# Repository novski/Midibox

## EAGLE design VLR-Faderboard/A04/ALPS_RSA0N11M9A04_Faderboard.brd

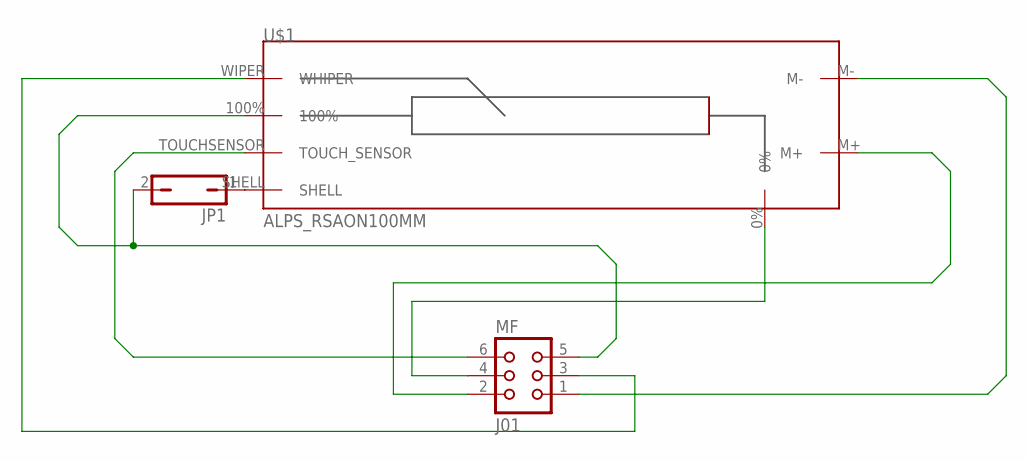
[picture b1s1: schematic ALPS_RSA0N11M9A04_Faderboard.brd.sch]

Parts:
JP1: JP1Q; JP1
MF: J01; CON06
U$1: ALPS_RSAON100MM; ALPS_RAS0N_MOTOR-FADER

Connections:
unnamed: MF.1, U$1.M-
unnamed: MF.2, U$1.M+
unnamed: MF.3, U$1.WIPER (WHIPER)
unnamed: MF.4, U$1.0%
unnamed: JP1.2, MF.5, U$1.100%
unnamed: MF.6, U$1.TOUCHSENSOR (TOUCH_SENSOR)
unnamed: JP1.1, U$1.SHELL

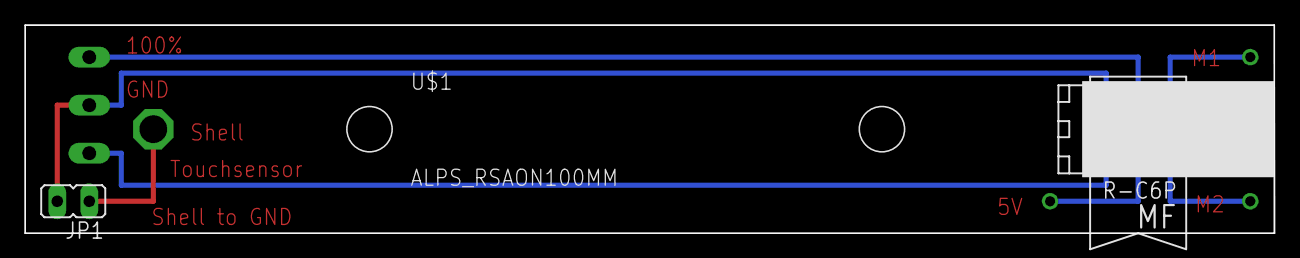
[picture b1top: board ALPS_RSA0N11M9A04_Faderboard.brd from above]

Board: 2 copper layers, 99.1 x 16.5 mm, 3 parts (0 on the bottom side), 7 nets.

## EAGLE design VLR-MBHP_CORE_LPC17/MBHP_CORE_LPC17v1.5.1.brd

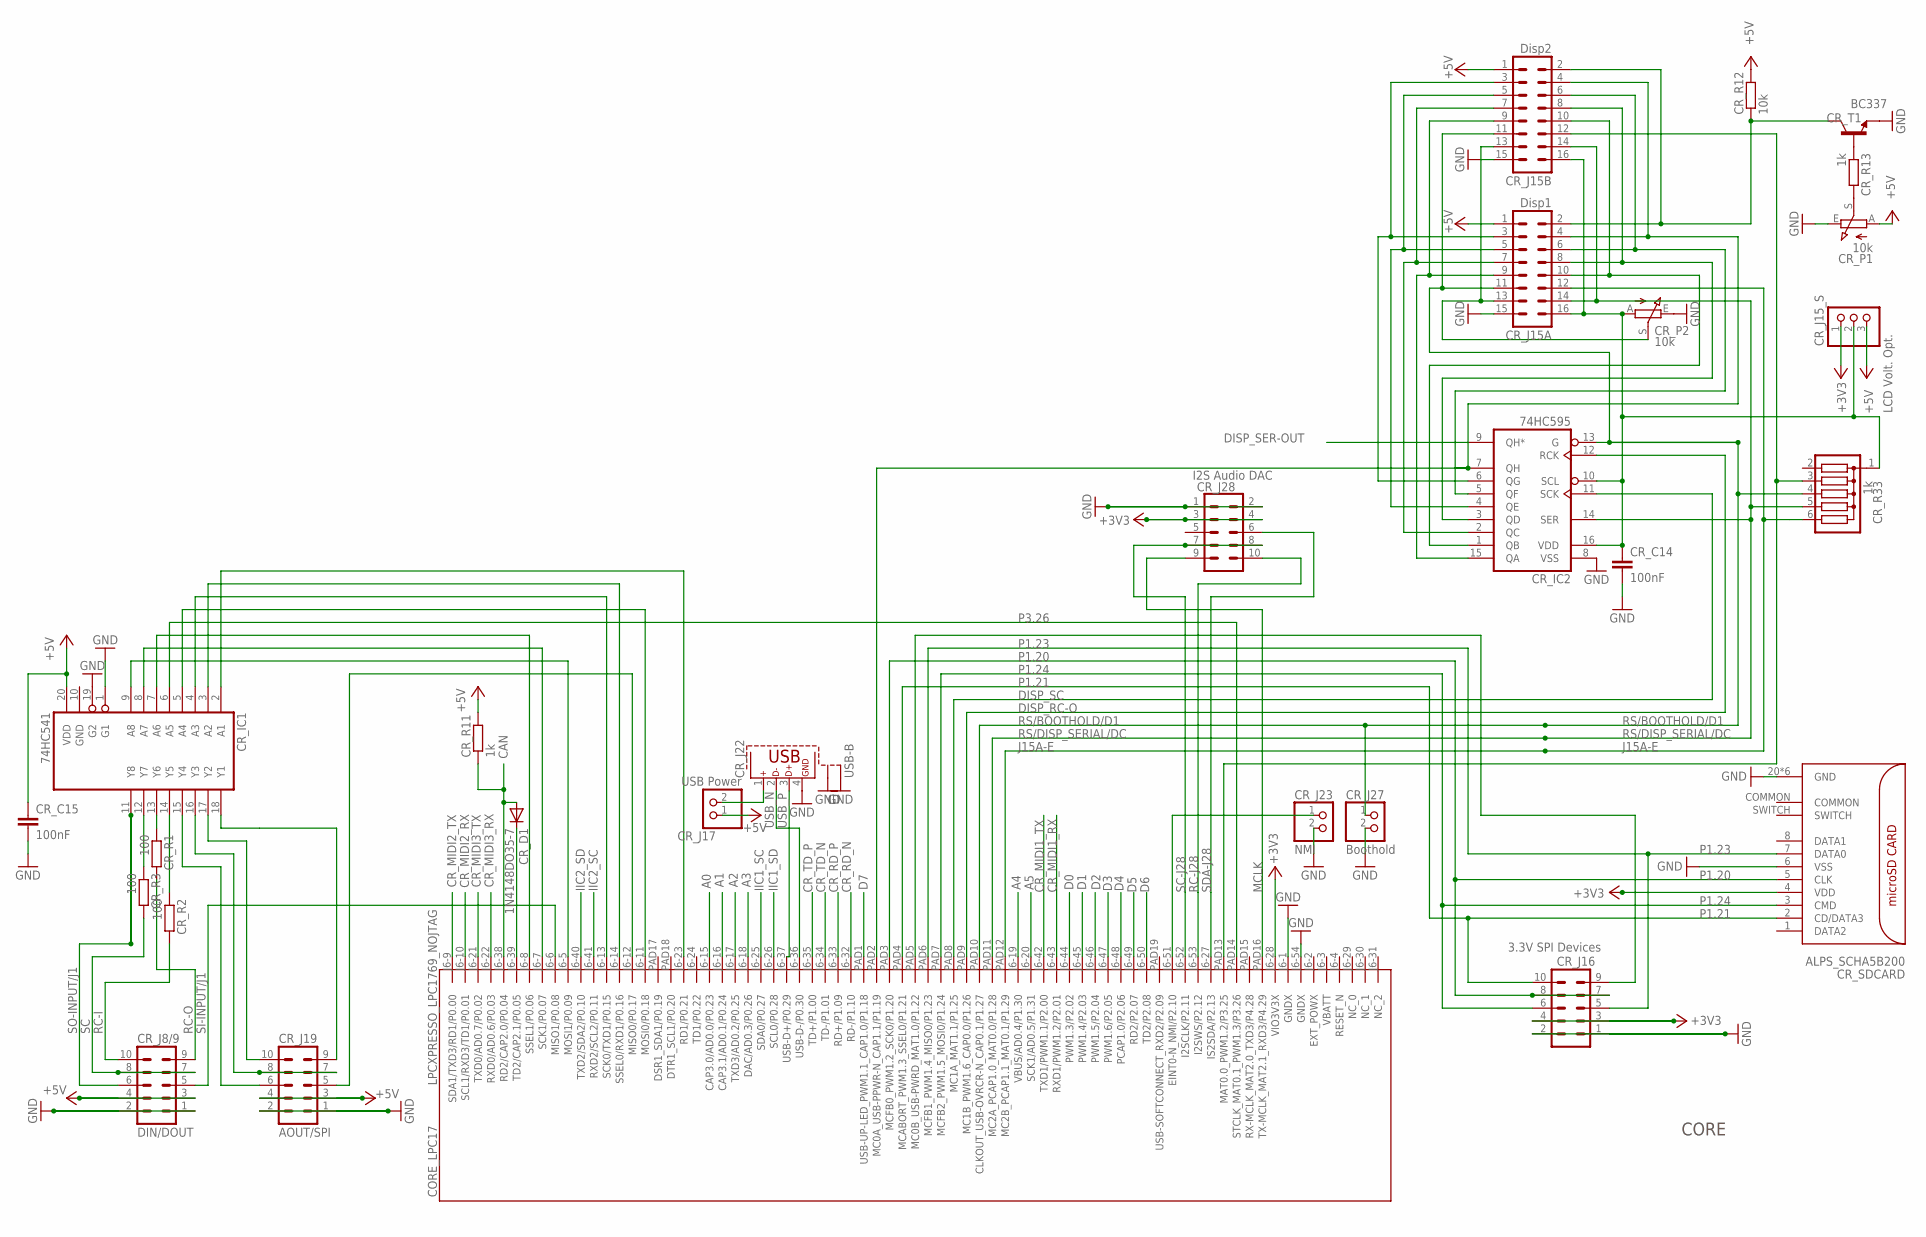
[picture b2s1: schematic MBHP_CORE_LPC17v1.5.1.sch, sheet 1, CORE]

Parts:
CORE_LPC17: LPCXPRESSO_LPC1769_NOJTAG; LPCEXPRESSO_CUT_NOJTAG
CR_C14, CR_C15: 100nF; C5B3
CR_D1: 1N4148DO35-7; DO35-7
CR_IC1: 74HC541; DIL20
CR_IC2: 74HC595; DIL16
CR_J8/9: DIN/DOUT; ML10
CR_J15A: Disp1; ML16
CR_J15B: Disp2; ML16
CR_J15_S: LCD Volt. Opt.; 1X03
CR_J16: 3.3V SPI Devices; ML10
CR_J17: USB Power; 1X02
CR_J19: AOUT/SPI; ML10
CR_J22: USB-B
CR_J23: NMI; 1X02
CR_J27: Boothold; 1X02
CR_J28: I2S Audio DAC; ML10
CR_P1, CR_P2: 10k; 6MM_V
CR_R1, CR_R2, CR_R3: 100; 0204/7
CR_R11, CR_R13: 1k; 0204/7
CR_R12: 10k; 0204/7
CR_R33: 1k; SIL6
CR_SDCARD: ALPS_SCHA5B200; ALPS_SCHA5B0200_MICRO_SD_PUSHPUSH
CR_T1: BC337; TO92

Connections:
+3V3: CORE_LPC17.J6-28 (VIO3V3X), CR_J15_S.1, CR_J16.3, CR_J16.4, CR_J28.3, CR_J28.4, CR_SDCARD.4 (VDD); also elsewhere on the board
+5V: CR_C15.1, CR_IC1.20 (VDD), CR_J8/9.3, CR_J8/9.4, CR_J15A.1, CR_J15B.1, CR_J15_S.3, CR_J17.1, CR_J19.3, CR_J19.4, CR_P1.A, CR_R11.2, CR_R12.2; also elsewhere on the board
A0: CORE_LPC17.J6-15 (CAP3.0/AD0.0/P0.23); also elsewhere on the board
A1: CORE_LPC17.J6-16 (CAP3.1/AD0.1/P0.24); also elsewhere on the board
A2: CORE_LPC17.J6-17 (TXD3/AD0.2/P0.25); also elsewhere on the board
A3: CORE_LPC17.J6-18 (DAC/AD0.3/P0.26); also elsewhere on the board
A4: CORE_LPC17.J6-19 (VBUS/AD0.4/P1.30); also elsewhere on the board
A5: CORE_LPC17.J6-20 (SCK1/AD0.5/P1.31); also elsewhere on the board
CAN: CORE_LPC17.J6-38 (RD2/CAP2.0/P0.04), CR_D1.A, CR_R11.1; also elsewhere on the board
CR_MIDI1_RX: CORE_LPC17.J6-43 (RXD1/PWM1.2/P2.01); also elsewhere on the board
CR_MIDI1_TX: CORE_LPC17.J6-42 (TXD1/PWM1.1/P2.00); also elsewhere on the board
CR_MIDI2_RX: CORE_LPC17.J6-10 (SCL1/RXD3/TD1/P0.01); also elsewhere on the board
CR_MIDI2_TX: CORE_LPC17.J6-9 (SDA1/TXD3/RD1/P0.00); also elsewhere on the board
CR_MIDI3_RX: CORE_LPC17.J6-22 (RXD0/AD0.6/P0.03); also elsewhere on the board
CR_MIDI3_TX: CORE_LPC17.J6-21 (TXD0/AD0.7/P0.02); also elsewhere on the board
CR_RD_N: CORE_LPC17.J6-32 (RD-/P1.10); also elsewhere on the board
CR_RD_P: CORE_LPC17.J6-33 (RD+/P1.09); also elsewhere on the board
CR_TD_N: CORE_LPC17.J6-34 (TD-/P1.01); also elsewhere on the board
CR_TD_P: CORE_LPC17.J6-35 (TD+/P1.00); also elsewhere on the board
D0: CORE_LPC17.J6-44 (PWM1.3/P2.02); also elsewhere on the board
D1: CORE_LPC17.J6-45 (PWM1.4/P2.03); also elsewhere on the board
D2: CORE_LPC17.J6-46 (PWM1.5/P2.04); also elsewhere on the board
D3: CORE_LPC17.J6-47 (PWM1.6/P2.05); also elsewhere on the board
D4: CORE_LPC17.J6-48 (PCAP1.0/P2.06); also elsewhere on the board
D5: CORE_LPC17.J6-49 (RD2/P2.07); also elsewhere on the board
D6: CORE_LPC17.J6-50 (TD2/P2.08); also elsewhere on the board
D7: CORE_LPC17.PAD1 (USB-UP-LED_PWM1.1_CAP1.0/P1.18); also elsewhere on the board
DISP_RC-O: CORE_LPC17.PAD9 (MC1B_PWM1.6_CAP0.0/P1.26), CR_IC2.12 (RCK)
DISP_SC: CORE_LPC17.PAD8 (MC1A_MAT1.1/P1.25), CR_IC2.11 (SCK)
DISP_SER-OUT: CR_IC2.9 (QH*)
GND: CORE_LPC17.J6-1 (GNDX), CORE_LPC17.J6-54 (GNDX), CR_C14.2, CR_C15.2, CR_IC1.1 (G1), CR_IC1.10 (GND), CR_IC1.19 (G2), CR_IC2.8 (VSS), CR_J8/9.1, CR_J8/9.2, CR_J15A.15, CR_J15B.15, CR_J16.1, CR_J16.2, CR_J19.1, CR_J19.2, CR_J22.4, CR_J22.S1, CR_J22.S2, CR_J23.2, CR_J27.2, CR_J28.1, CR_J28.2, CR_P1.E, CR_P2.E, CR_SDCARD.6 (VSS), CR_SDCARD.20 (GND), CR_SDCARD.21 (GND), CR_SDCARD.22 (GND), CR_SDCARD.23 (GND), CR_SDCARD.24 (GND), CR_SDCARD.25 (GND), CR_T1.1 (E); also elsewhere on the board
IIC1_SC: CORE_LPC17.J6-25 (SDA0/P0.27); also elsewhere on the board
IIC1_SD: CORE_LPC17.J6-26 (SCL0/P0.28); also elsewhere on the board
IIC2_SC: CORE_LPC17.J6-41 (RXD2/SCL2/P0.11); also elsewhere on the board
IIC2_SD: CORE_LPC17.J6-40 (TXD2/SDA2/P0.10); also elsewhere on the board
J15A-E: CORE_LPC17.PAD12 (MC2B_PCAP1.1_MAT0.1/P1.29), CR_J15A.12, CR_R33.6
J15B-E2: CORE_LPC17.PAD13 (MAT0.0_PWM1.2/P3.25), CR_J15B.12, CR_R33.3; also elsewhere on the board
LCD_VOLTAGE_OPTION: CR_C14.1, CR_IC2.10 (SCL), CR_IC2.16 (VDD), CR_J15A.16, CR_J15B.16, CR_J15_S.2, CR_P2.A, CR_R33.1; also elsewhere on the board
MCLK: CORE_LPC17.PAD16 (TX-MCLK_MAT2.1_RXD3/P4.29), CR_J28.9
unnamed: CR_IC2.6 (QG), CR_J15A.3, CR_J15B.3
unnamed: CR_IC2.5 (QF), CR_J15A.6, CR_J15B.6
unnamed: CR_IC2.4 (QE), CR_J15A.5, CR_J15B.5
unnamed: CR_IC2.3 (QD), CR_J15A.8, CR_J15B.8
unnamed: CORE_LPC17.J6-39 (TD2/CAP2.1/P0.05), CR_D1.C
unnamed: CR_IC2.2 (QC), CR_J15A.7, CR_J15B.7
unnamed: CR_IC2.1 (QB), CR_J15A.10, CR_J15B.10
unnamed: CR_IC2.15 (QA), CR_J15A.9, CR_J15B.9
unnamed: CORE_LPC17.J6-51 (EINT0-N_NMI/P2.10), CR_J23.1
unnamed: CR_J15A.13, CR_J15B.13, CR_P2.S
unnamed: CR_IC1.15 (Y4), CR_J19.6
unnamed: CR_P1.S, CR_R13.2
unnamed: CR_R13.1, CR_T1.2 (B)
unnamed: CR_J15A.2, CR_J15B.2, CR_R12.1, CR_T1.3 (C)
unnamed: CR_IC1.17 (Y2), CR_J19.10
unnamed: CR_IC1.18 (Y1), CR_J19.9
unnamed: CR_IC1.16 (Y3), CR_J19.7, CR_J19.8
unnamed: CORE_LPC17.J6-12 (MISO0/P0.17), CR_J19.5
unnamed: CORE_LPC17.PAD5 (MC0B_USB-PWRD_MAT1.0/P1.22), CR_J16.9
unnamed: CR_J17.2, CR_J22.1
unnamed: CORE_LPC17.PAD2 (MC0A_USB-PPWR-N_CAP1.1/P1.19), CR_IC2.7 (QH), CR_J15A.4, CR_J15B.4
unnamed: CORE_LPC17.J6-14 (SSEL0/RXD1/P0.16), CR_IC1.3 (A2)
unnamed: CORE_LPC17.J6-23 (RD1/P0.21), CR_IC1.2 (A1)
unnamed: CORE_LPC17.J6-13 (SCK0/TXD1/P0.15), CR_IC1.4 (A3)
unnamed: CORE_LPC17.J6-11 (MOSI0/P0.18), CR_IC1.5 (A4)
unnamed: CORE_LPC17.J6-8 (SSEL1/P0.06), CR_IC1.7 (A6)
unnamed: CORE_LPC17.J6-7 (SCK1/P0.07), CR_IC1.8 (A7)
unnamed: CORE_LPC17.J6-5 (MOSI1/P0.09), CR_IC1.9 (A8)
P1.20: CORE_LPC17.PAD3 (MCFB0_PWM1.2_SCK0/P1.20), CR_J16.7, CR_J16.8, CR_SDCARD.5 (CLK)
P1.21: CORE_LPC17.PAD4 (MCABORT_PWM1.3_SSEL0/P1.21), CR_J16.10, CR_SDCARD.2 (CD/DATA3)
P1.23: CORE_LPC17.PAD6 (MCFB1_PWM1.4_MISO0/P1.23), CR_J16.5, CR_SDCARD.7 (DATA0)
P1.24: CORE_LPC17.PAD7 (MCFB2_PWM1.5_MOSI0/P1.24), CR_J16.6, CR_SDCARD.3 (CMD)
P3.26: CORE_LPC17.PAD14 (STCLK_MAT0.1_PWM1.3/P3.26), CR_IC1.6 (A5)
RC-I: CR_J8/9.10, CR_R2.2
RC-I-: CR_IC1.14 (Y5), CR_R2.1
RC-J28: CORE_LPC17.J6-53 (I2SWS/P2.12), CR_J28.10; also elsewhere on the board
RC-O: CR_J8/9.9, CR_R1.2
RC-O-: CR_IC1.13 (Y6), CR_R1.1
RS/BOOTHOLD/D1: CORE_LPC17.PAD10 (CLKOUT_USB-OVRCR-N_CAP0.1/P1.27), CR_IC2.13 (G), CR_J15A.11, CR_J15B.11, CR_J27.1, CR_R33.4; also elsewhere on the board
RS/DISP_SERIAL/DC: CORE_LPC17.PAD11 (MC2A_PCAP1.0_MAT0.0/P1.28), CR_IC2.14 (SER), CR_J15A.14, CR_J15B.14, CR_R33.5; also elsewhere on the board
SC: CR_J8/9.7, CR_J8/9.8, CR_R3.2
SC-: CR_IC1.12 (Y7), CR_R3.1
SC-J28: CORE_LPC17.J6-52 (I2SCLK/P2.11), CR_J28.7, CR_J28.8; also elsewhere on the board
SDA-J28: CORE_LPC17.J6-27 (IS2SDA/P2.13), CR_J28.6; also elsewhere on the board
SI-INPUT/J1: CORE_LPC17.J6-6 (MISO1/P0.08), CR_J8/9.5
SO-INPUT/J1: CR_IC1.11 (Y8), CR_J8/9.6
USB_N: CORE_LPC17.J6-36 (USB-D-/P0.30), CR_J22.2
USB_P: CORE_LPC17.J6-37 (USB-D+/P0.29), CR_J22.3

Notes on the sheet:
CORE

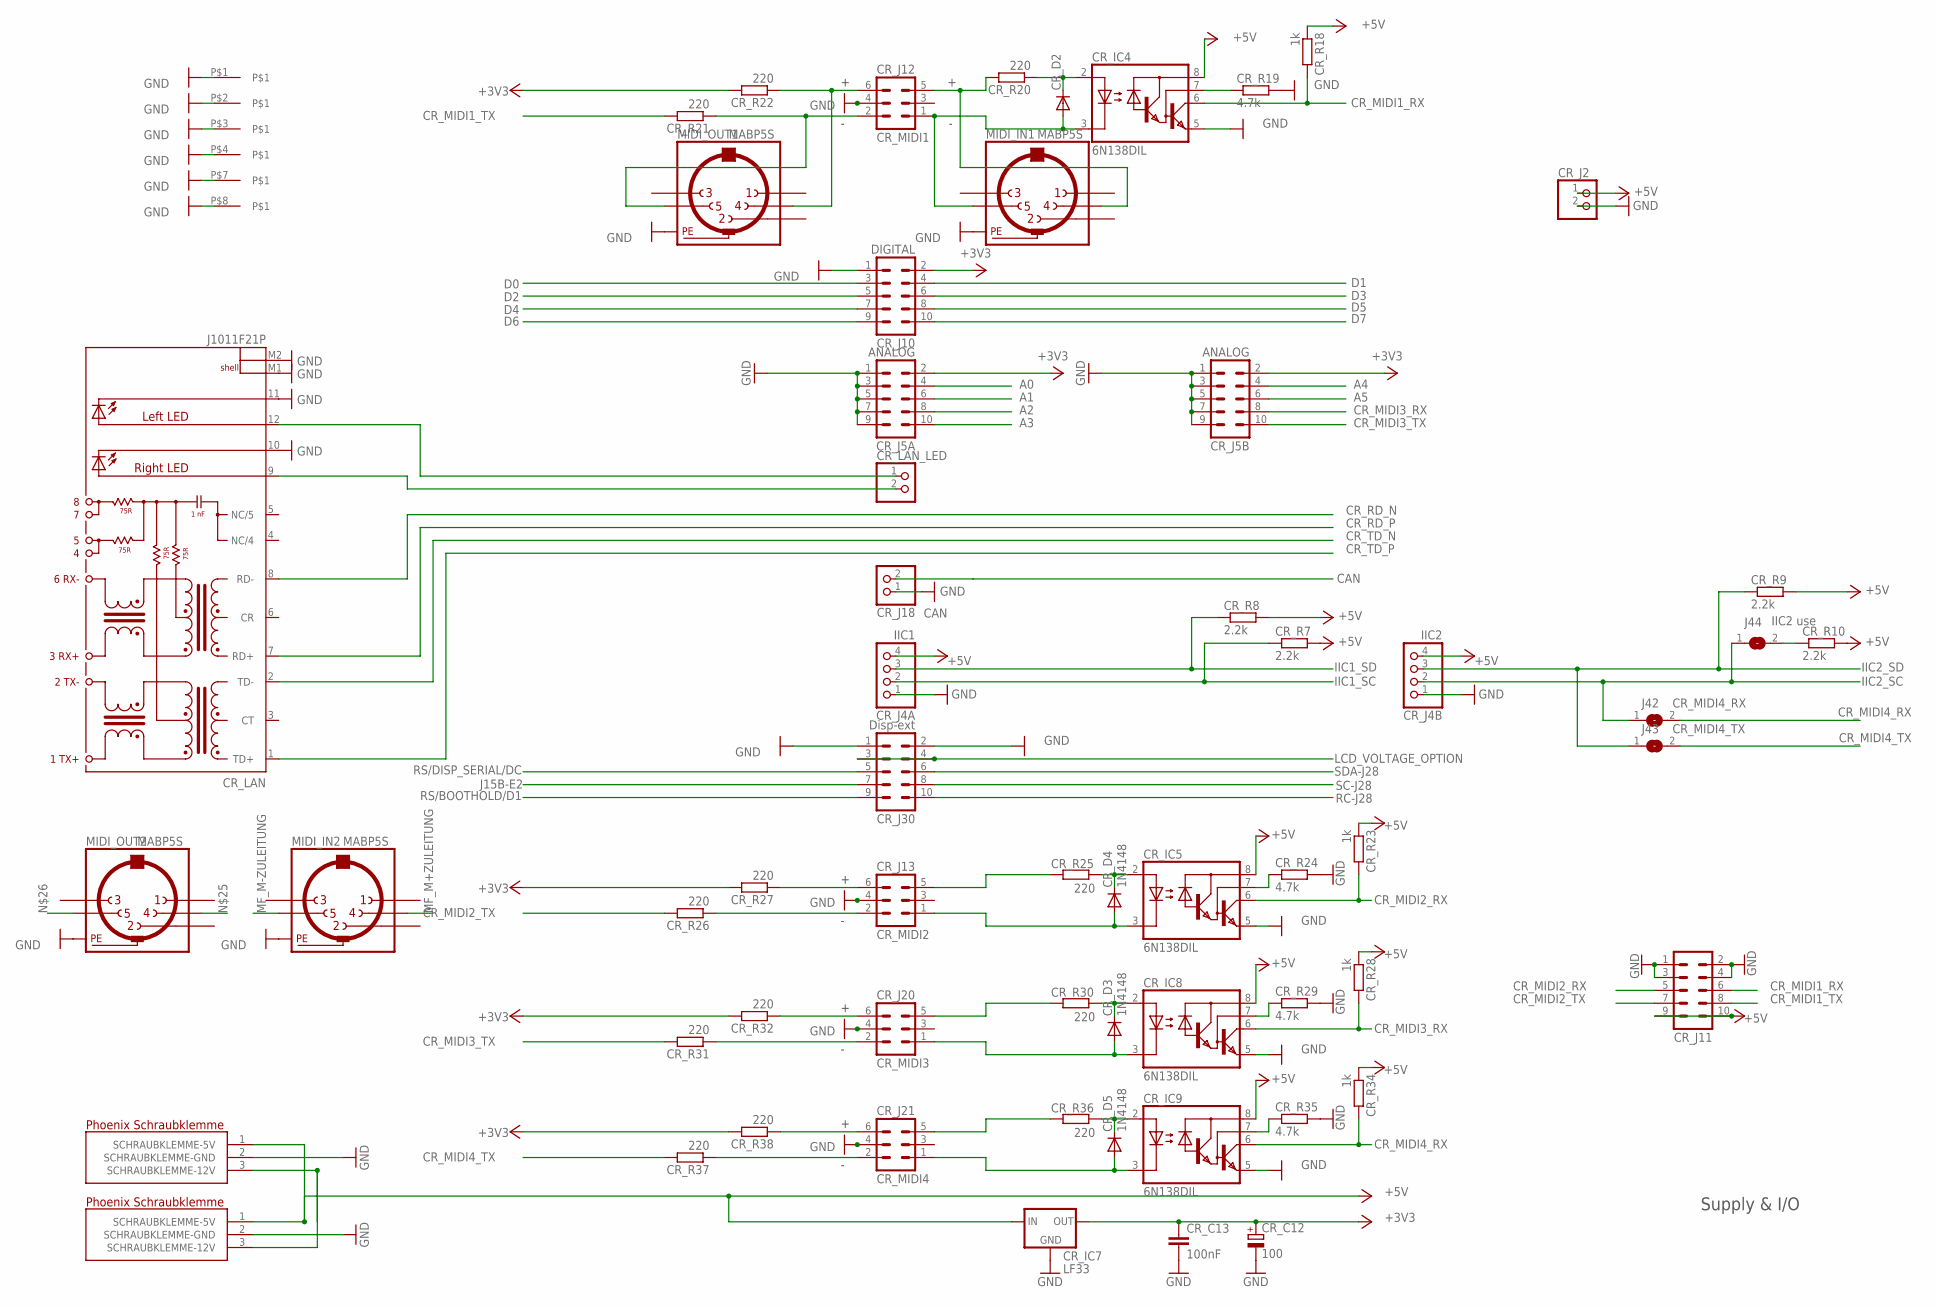
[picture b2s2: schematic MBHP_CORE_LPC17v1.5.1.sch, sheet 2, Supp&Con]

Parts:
CR_C12: 100; E5-10,5
CR_C13: 100nF; C5B3
CR_D2: 1N4148DO35-7; DO35-7
CR_D3, CR_D4, CR_D5: 1N4148; DO35-7
CR_IC4, CR_IC5, CR_IC8, CR_IC9: 6N138DIL; DIL08
CR_IC7: LF33; TO220
CR_J2: PINHD-1X2; 1X02
CR_J4A: IIC1; 1X04
CR_J4B: IIC2; 1X04
CR_J5A, CR_J5B: ANALOG; ML10
CR_J10: DIGITAL; ML10
CR_J11: ML10
CR_J12: CR_MIDI1; ML6
CR_J13: CR_MIDI2; ML6
CR_J18: CAN; 1X02
CR_J20: CR_MIDI3; ML6
CR_J21: CR_MIDI4; ML6
CR_J30: Disp-ext; ML10
CR_LAN: J1011F21P; J1
CR_LAN_LED: PINHD-1X2; 1X02
CR_R7, CR_R8, CR_R9, CR_R10: 2.2k; 0204/7
CR_R18, CR_R23, CR_R28, CR_R34: 1k; 0204/7
CR_R19, CR_R24, CR_R29, CR_R35: 4.7k; 0204/7
CR_R20, CR_R21, CR_R22, CR_R25, CR_R26, CR_R27, CR_R30, CR_R31, CR_R32, CR_R36, CR_R37, CR_R38: 220; 0204/7
J42: CR_MIDI4_RX; SJ
J43: CR_MIDI4_TX; SJ
J44: IIC2 use; SJ
KLEMME1, KLEMME2: PT-1.5/3; PT-1.5/3-5.0
MIDI_IN1, MIDI_IN2: MABP5S
MIDI_OUT1, MIDI_OUT2: MABP5S
U$2: MIDIBOX_FULL; MIDIBOX14X12

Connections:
+3V3: CR_C12.+, CR_C13.1, CR_IC7.OUT, CR_J5A.2, CR_J5B.2, CR_J10.2, CR_R22.2, CR_R27.2, CR_R32.2, CR_R38.2; also elsewhere on the board
+5V: CR_IC4.8 (VCC), CR_IC5.8 (VCC), CR_IC7.IN, CR_IC8.8 (VCC), CR_IC9.8 (VCC), CR_J2.1, CR_J4A.4, CR_J4B.4, CR_J11.9, CR_J11.10, CR_R7.2, CR_R8.2, CR_R9.2, CR_R10.2, CR_R18.1, CR_R23.1, CR_R28.1, CR_R34.1, KLEMME1.1 (SCHRAUBKLEMME-5V), KLEMME2.1 (SCHRAUBKLEMME-5V); also elsewhere on the board
+12V: KLEMME1.3 (SCHRAUBKLEMME-12V), KLEMME2.3 (SCHRAUBKLEMME-12V)
A0: CR_J5A.4; also elsewhere on the board
A1: CR_J5A.6; also elsewhere on the board
A2: CR_J5A.8; also elsewhere on the board
A3: CR_J5A.10; also elsewhere on the board
A4: CR_J5B.4; also elsewhere on the board
A5: CR_J5B.6; also elsewhere on the board
CAN: CR_J18.2; also elsewhere on the board
CR_LEFT_LED: CR_LAN.12 (AL), CR_LAN_LED.1
CR_M1+: CR_J12.5, CR_R20.2, MIDI_IN1.4
CR_M1-: CR_D2.A, CR_IC4.3 (C), CR_J12.1, MIDI_IN1.5
CR_M2+$1: CR_D2.C, CR_IC4.2 (A), CR_R20.1
CR_MIDI1_RX: CR_IC4.6 (VO), CR_J11.6, CR_R18.2; also elsewhere on the board
CR_MIDI1_TX: CR_J11.8, CR_R21.2; also elsewhere on the board
CR_MIDI2_RX: CR_IC5.6 (VO), CR_J11.5, CR_R23.2; also elsewhere on the board
CR_MIDI2_TX: CR_J11.7, CR_R26.2; also elsewhere on the board
CR_MIDI3_RX: CR_IC8.6 (VO), CR_J5B.8, CR_R28.2; also elsewhere on the board
CR_MIDI3_TX: CR_J5B.10, CR_R31.2; also elsewhere on the board
CR_MIDI4_RX: CR_IC9.6 (VO), CR_R34.2, J42.2
CR_MIDI4_TX: CR_R37.2, J43.2
CR_RD_N: CR_LAN.8 (RD-); also elsewhere on the board
CR_RD_P: CR_LAN.7 (RD+); also elsewhere on the board
CR_RIGHT_LED: CR_LAN.9 (A-R), CR_LAN_LED.2
CR_TD_N: CR_LAN.2 (TD-); also elsewhere on the board
CR_TD_P: CR_LAN.1 (TD+); also elsewhere on the board
D0: CR_J10.3; also elsewhere on the board
D1: CR_J10.4; also elsewhere on the board
D2: CR_J10.5; also elsewhere on the board
D3: CR_J10.6; also elsewhere on the board
D4: CR_J10.7; also elsewhere on the board
D5: CR_J10.8; also elsewhere on the board
D6: CR_J10.9; also elsewhere on the board
D7: CR_J10.10; also elsewhere on the board
GND: CR_C12.-, CR_C13.2, CR_IC4.5 (GND), CR_IC5.5 (GND), CR_IC7.GND, CR_IC8.5 (GND), CR_IC9.5 (GND), CR_J2.2, CR_J4A.1, CR_J4B.1, CR_J5A.1, CR_J5A.3, CR_J5A.5, CR_J5A.7, CR_J5A.9, CR_J5B.1, CR_J5B.3, CR_J5B.5, CR_J5B.7, CR_J5B.9, CR_J10.1, CR_J11.1, CR_J11.2, CR_J11.3, CR_J11.4, CR_J12.4, CR_J13.4, CR_J18.1, CR_J20.4, CR_J21.4, CR_J30.1, CR_J30.2, CR_LAN.10 (C-R), CR_LAN.11 (C-L), CR_LAN.M1 (AL1), CR_LAN.M2 (AL2), CR_R19.2, CR_R24.2, CR_R29.2, CR_R35.2, KLEMME1.2 (SCHRAUBKLEMME-GND), KLEMME2.2 (SCHRAUBKLEMME-GND), MIDI_IN1.PE, MIDI_IN1.PE@ (PE), MIDI_IN2.PE, MIDI_IN2.PE@ (PE), MIDI_OUT1.PE, MIDI_OUT1.PE@ (PE), MIDI_OUT2.PE, MIDI_OUT2.PE@ (PE), U$2.P$1, U$2.P$2, U$2.P$3, U$2.P$4, U$2.P$7, U$2.P$8; also elsewhere on the board
IIC1_SC: CR_J4A.2, CR_R7.1; also elsewhere on the board
IIC1_SD: CR_J4A.3, CR_R8.1; also elsewhere on the board
IIC2_SC: CR_J4B.2, J42.1, J44.1; also elsewhere on the board
IIC2_SD: CR_J4B.3, CR_R9.1, J43.1; also elsewhere on the board
J15B-E2: CR_J30.7; also elsewhere on the board
LCD_VOLTAGE_OPTION: CR_J30.3, CR_J30.4; also elsewhere on the board
MF_M+ZULEITUNG: CR_J13.5, CR_R25.2, MIDI_IN2.4
MF_M+ZULEITUNG1: CR_J20.5, CR_R30.2
MF_M+ZULEITUNG2: CR_J21.5, CR_R36.2
MF_M-ZULEITUNG: CR_D4.A, CR_IC5.3 (C), CR_J13.1, MIDI_IN2.5
MF_M-ZULEITUNG1: CR_D3.A, CR_IC8.3 (C), CR_J20.1
MF_M-ZULEITUNG2: CR_D5.A, CR_IC9.3 (C), CR_J21.1
unnamed: CR_J12.6, CR_R22.1, MIDI_OUT1.4
unnamed: CR_IC4.7 (VB), CR_R19.1
unnamed: CR_D4.C, CR_IC5.2 (A), CR_R25.1
unnamed: CR_J13.6, CR_R27.1, MIDI_OUT2.4
unnamed: CR_J13.2, CR_R26.1, MIDI_OUT2.5
unnamed: CR_D3.C, CR_IC8.2 (A), CR_R30.1
unnamed: CR_IC8.7 (VB), CR_R29.1
unnamed: CR_J20.6, CR_R32.1
unnamed: CR_J20.2, CR_R31.1
unnamed: CR_D5.C, CR_IC9.2 (A), CR_R36.1
unnamed: CR_IC9.7 (VB), CR_R35.1
unnamed: CR_J21.6, CR_R38.1
unnamed: CR_J21.2, CR_R37.1
unnamed: CR_R10.1, J44.2
unnamed: CR_J12.2, CR_R21.1, MIDI_OUT1.5
unnamed: CR_IC5.7 (VB), CR_R24.1
RC-J28: CR_J30.10; also elsewhere on the board
RS/BOOTHOLD/D1: CR_J30.9; also elsewhere on the board
RS/DISP_SERIAL/DC: CR_J30.5; also elsewhere on the board
SC-J28: CR_J30.8; also elsewhere on the board
SDA-J28: CR_J30.6; also elsewhere on the board

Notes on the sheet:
Supply & I/O

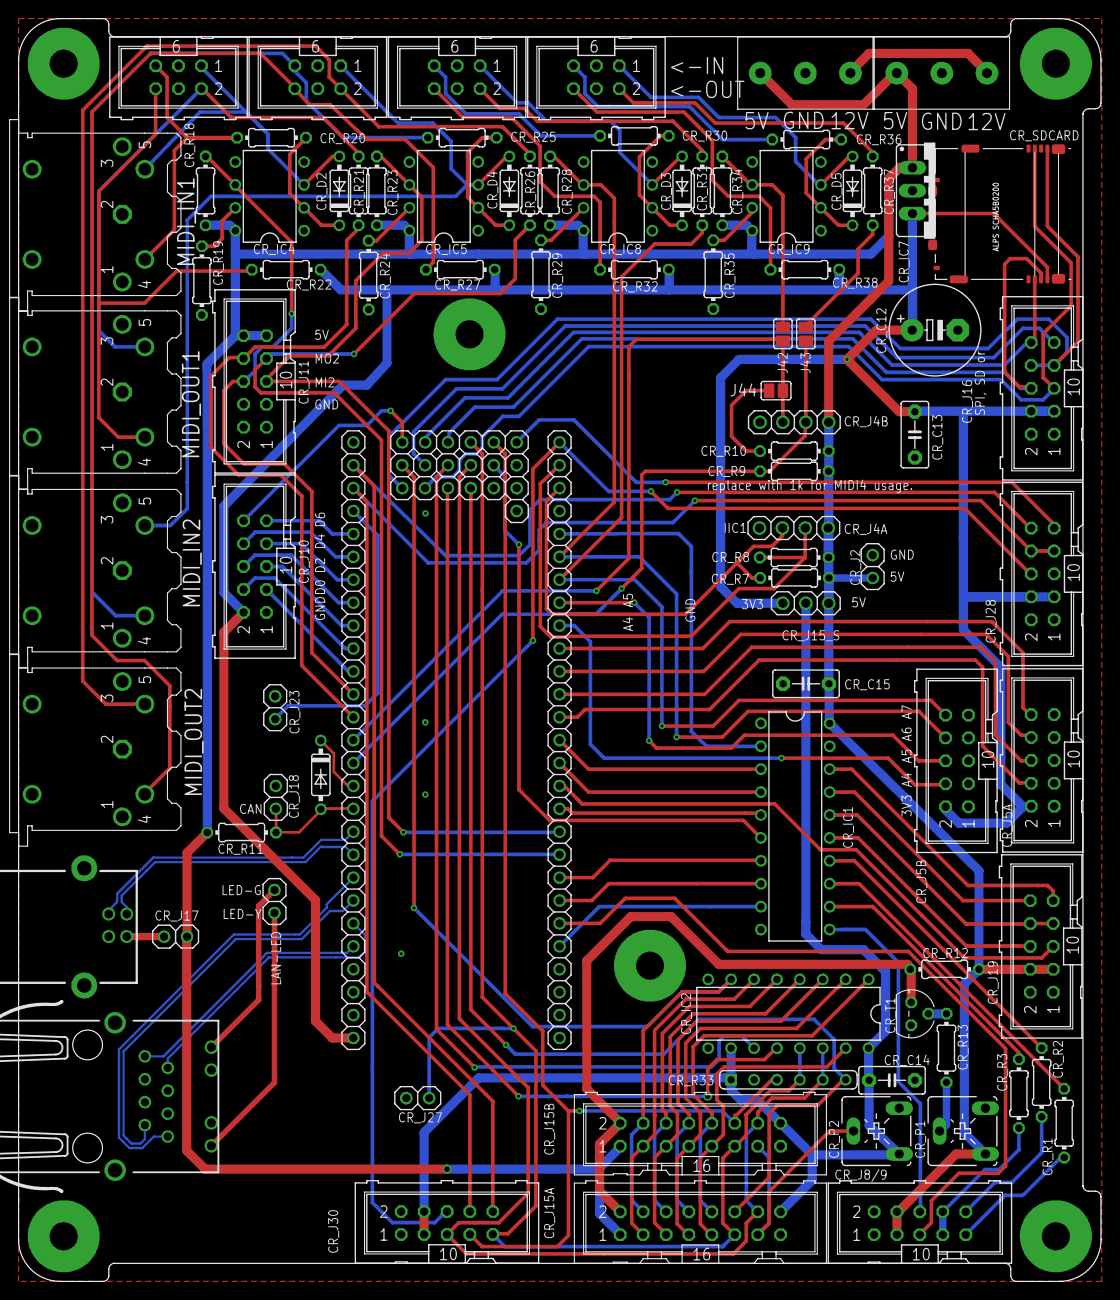
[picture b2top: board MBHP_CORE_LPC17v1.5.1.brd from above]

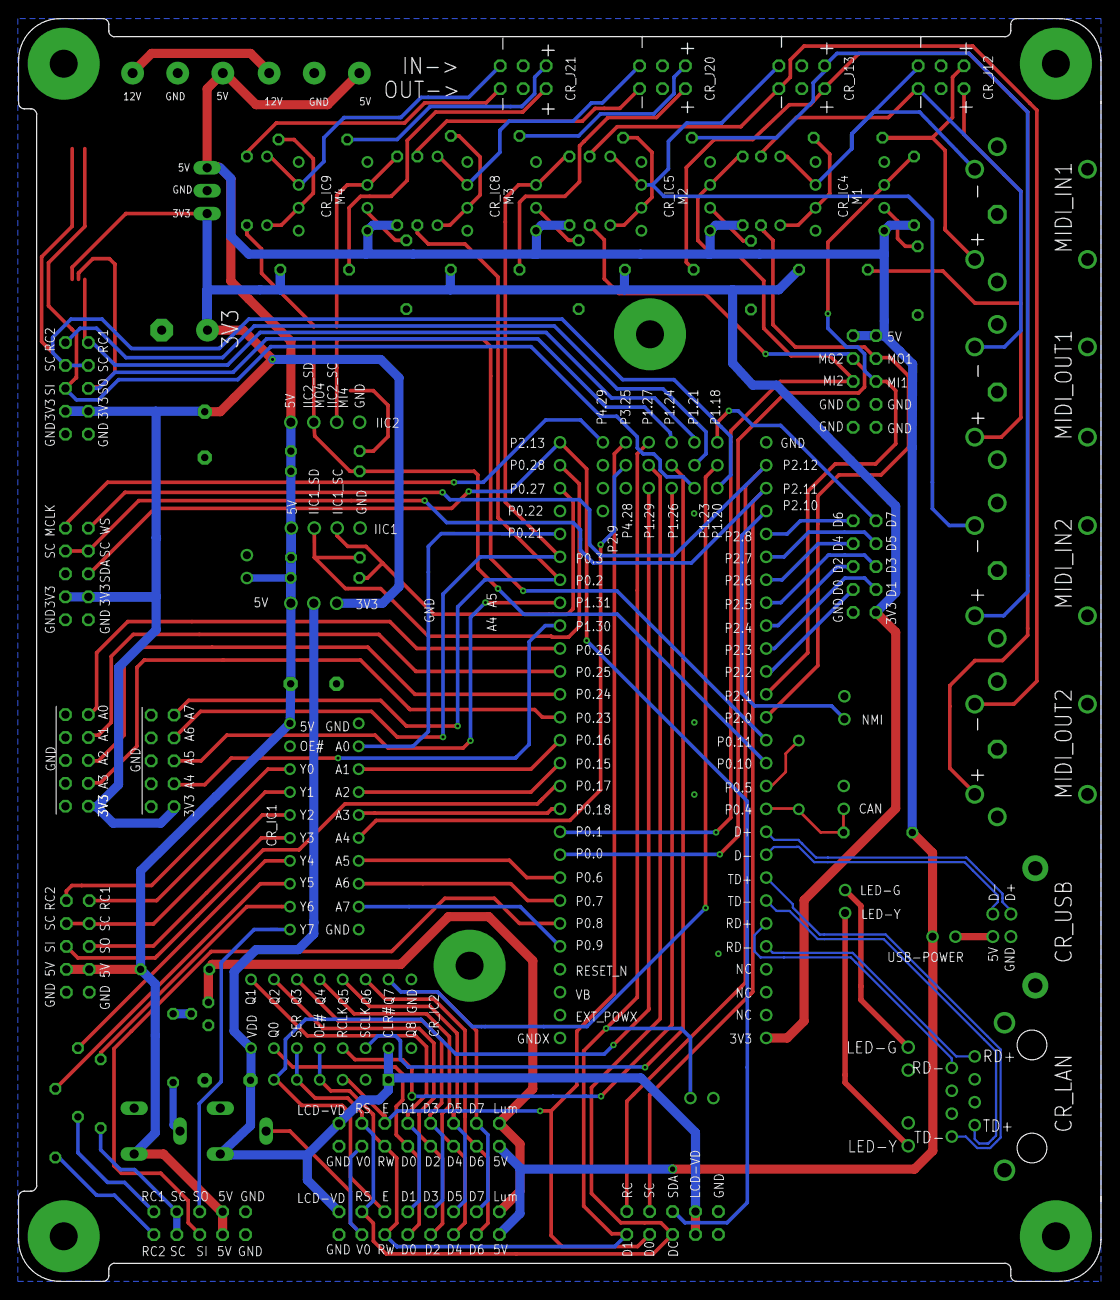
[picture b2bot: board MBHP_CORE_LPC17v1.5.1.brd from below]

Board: 2 copper layers, 120.0 x 140.0 mm, 92 parts (2 on the bottom side), 116 nets.

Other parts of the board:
U$5, U$8: CORE_LPC17
U$6, U$7: VLRLAB
